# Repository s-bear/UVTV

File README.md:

# UVTV
RGB-V-UV LED display, as published in "A five-channel LED display to investigate UV perception" in Methods in Ecology and Evolution, 2021.

## TO DO
- Display: Compactness and seamless edge-to-edge display panelling is *not* a priority any more. There are a few places where these design goals made things quite difficult and any new production should have these changes made:
  - [ ] Point-of-Load power supply on display board for LEDs.
  - [ ] Separate LED power from TLC5955 power.
  - [ ] Increase margins and put mounting holes in sane places.
  - [ ] Use larger connectors for the flat-flex cables. Assess signal integrity and see if more conductors would be useful for shielding.
  - [ ] Another layer of PCB might be in order to ease routing of control signals, especially if there are signal integrity issues at higher speeds.
- Controller: A higher-speed controller is necessary to use the full potential of the display panel. There are several viable alternatives:
  1. A high-speed microcontroller module, such as the Teensy 4.1 (600 MHz), using built-in SPI or bit-banging to communicate with TLC5955 chips.
  2. A microcontroller + FPGA combo -- using the microcontroller to handle USB and FPGA to handle the TLC5955 communication.
  3. An FPGA to handle both USB and TLC5955.
- 3D Models
  - [ ] Redraw in an open source CAD tool, e.g. FreeCAD.

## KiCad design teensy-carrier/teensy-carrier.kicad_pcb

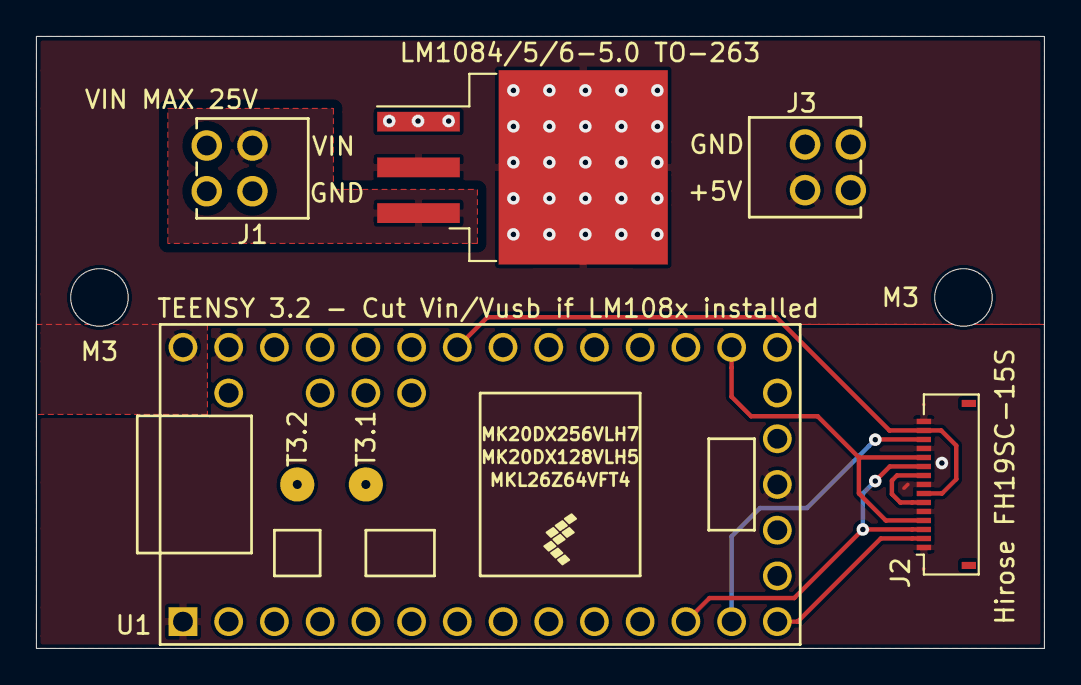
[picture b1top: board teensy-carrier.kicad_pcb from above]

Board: 2 copper layers, 56.0 x 34.0 mm, 5 parts (0 on the bottom side), 9 nets.

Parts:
J1: Conn_01x02_Male; TerminalBlock_DECA-MB312-254-2
J2: Conn_01x15_Female; Hirose_FH19SC-15S-0.5SH_1x15-1MP_P0.50mm_Horizontal
J3: Conn_01x02_Female; TerminalBlock_DECA-MB312-254-2
U1: Teensy3.2; Teensy30_31_32_LC
U2: LM1084-5.0; TO-263-3_TabPin2

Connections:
+5V: J3.2, U1.33, U2.2
/GCLK: J2.7, J2.14, U1.27
/LAT: J2.3, J2.10, U1.12
/SCLK: J2.4, J2.11, U1.21
/SIN1: J2.13, U1.13
/SOUT1_SIN2: J2.6, J2.9
/SOUT2: J2.2, U1.14
GND: J1.1, J2.1, J2.5, J2.8, J2.12, J2.15, J3.1, U1.1, U1.17, U1.32, U2.1
unnamed: J1.2, U2.3

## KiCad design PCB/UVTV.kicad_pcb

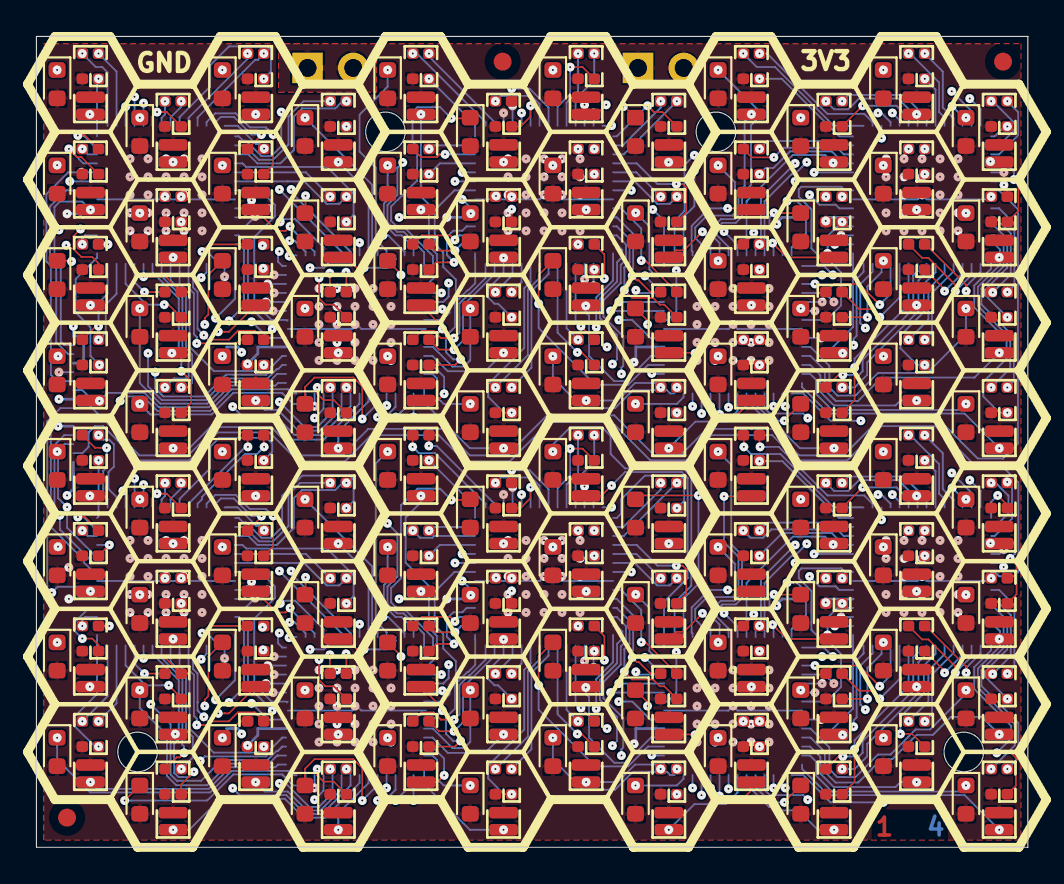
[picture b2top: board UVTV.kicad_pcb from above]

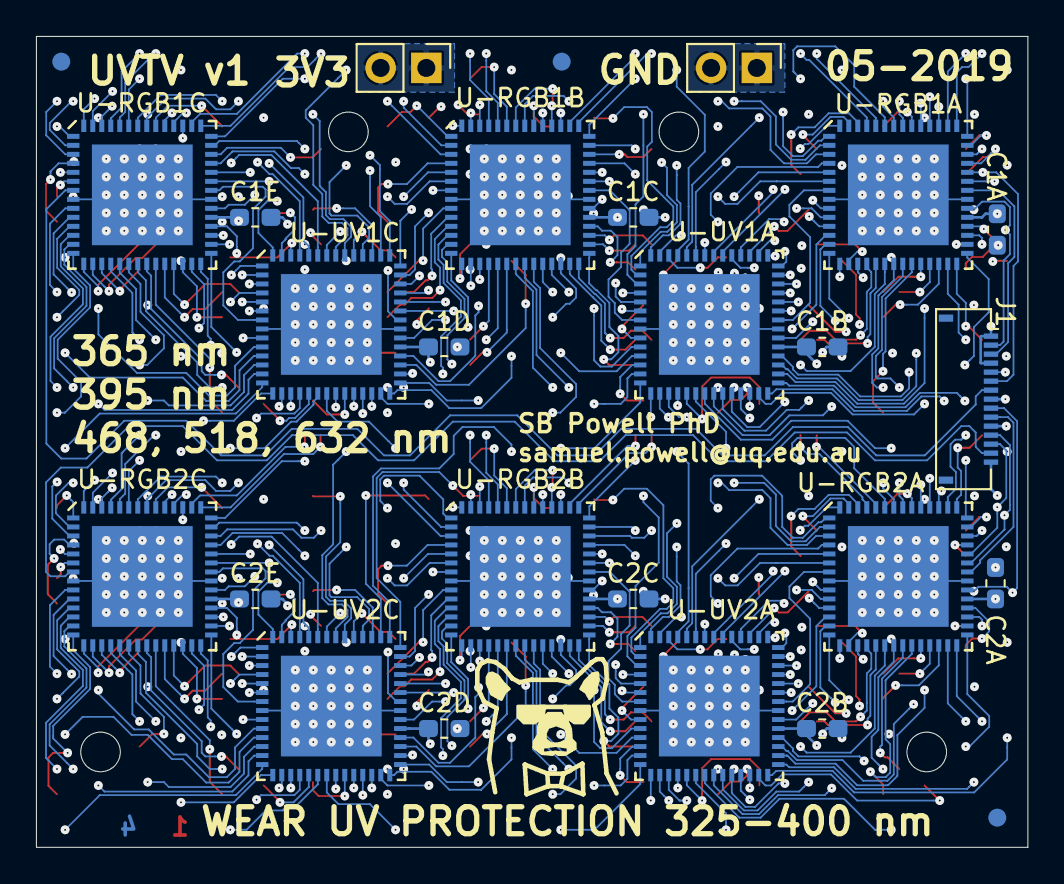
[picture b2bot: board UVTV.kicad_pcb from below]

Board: 4 copper layers, 55.1 x 45.0 mm, 321 parts (26 on the bottom side), 500 nets.

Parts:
C1A, C1B, C1C, C1D, C1E, C2A, C2B, C2C, C2D, C2E: 0.1u; C_0603_1608Metric_Pad1.05x0.95mm_HandSolder
FID1, FID2, FID3, FID4, FID5, FID6: Fiducial_1mm_Dia_2mm_Outer
J1: Conn_01x15; Hirose_FH19SC-15S-0.5SH_1x15-1MP_P0.50mm_Horizontal
J2: Conn_01x02; PinHeader_1x02_P2.54mm_Vertical
J3: Conn_01x03; PinHeader_1x02_P2.54mm_Vertical
MH1A, MH1B, MH2A, MH2B: MountingHole; MountingHole_2.2mm_M2
RGB1A0, RGB1A1, RGB1A2, RGB1A3, RGB1A4, RGB1A5, RGB1A6, RGB1A7, RGB1A8, RGB1A9, RGB1A10, RGB1A11, RGB1A12, RGB1A13, RGB1A14, RGB1A15, RGB1B0, RGB1B1, RGB1B2, RGB1B3, RGB1B4, RGB1B5, RGB1B6, RGB1B7, RGB1B8, RGB1B9, RGB1B10, RGB1B11, RGB1B12, RGB1B13, RGB1B14, RGB1B15, RGB1C0, RGB1C1, RGB1C2, RGB1C3, RGB1C4, RGB1C5, RGB1C6, RGB1C7, RGB1C8, RGB1C9, RGB1C10, RGB1C11, RGB1C12, RGB1C13, RGB1C14, RGB1C15, RGB2A0, RGB2A1, RGB2A2, RGB2A3, RGB2A4, RGB2A5, RGB2A6, RGB2A7, RGB2A8, RGB2A9, RGB2A10, RGB2A11, RGB2A12, RGB2A13, RGB2A14, RGB2A15, RGB2B0, RGB2B1, RGB2B2, RGB2B3, RGB2B4, RGB2B5, RGB2B6, RGB2B7, RGB2B8, RGB2B9, RGB2B10, RGB2B11, RGB2B12, RGB2B13, RGB2B14, RGB2B15, RGB2C0, RGB2C1, RGB2C2, RGB2C3, RGB2C4, RGB2C5, RGB2C6, RGB2C7, RGB2C8, RGB2C9, RGB2C10, RGB2C11, RGB2C12, RGB2C13, RGB2C14, RGB2C15: EAST1616RGB; EAST1616RGBA
U-RGB1A, U-RGB1B, U-RGB1C, U-RGB2A, U-RGB2B, U-RGB2C: TLC5955-RTQ; QFN-56-1EP_8x8mm_P0.5mm_EP5.6x5.6mm
U-UV1A, U-UV1C, U-UV2A, U-UV2C: TLC5955-RTQ; QFN-56-1EP_8x8mm_P0.5mm_EP5.6x5.6mm
UV1A0, UV1A1, UV1A2, UV1A3, UV1A4, UV1A5, UV1A6, UV1A7, UV1A8, UV1A9, UV1A10, UV1A11, UV1A12, UV1A13, UV1A14, UV1A15, UV1B0, UV1B1, UV1B2, UV1B3, UV1B4, UV1B5, UV1B6, UV1B7, UV1B8, UV1B9, UV1B10, UV1B11, UV1B12, UV1B13, UV1B14, UV1B15, UV1C0, UV1C1, UV1C2, UV1C3, UV1C4, UV1C5, UV1C6, UV1C7, UV1C8, UV1C9, UV1C10, UV1C11, UV1C12, UV1C13, UV1C14, UV1C15, UV2A0, UV2A1, UV2A2, UV2A3, UV2A4, UV2A5, UV2A6, UV2A7, UV2A8, UV2A9, UV2A10, UV2A11, UV2A12, UV2A13, UV2A14, UV2A15, UV2B0, UV2B1, UV2B2, UV2B3, UV2B4, UV2B5, UV2B6, UV2B7, UV2B8, UV2B9, UV2B10, UV2B11, UV2B12, UV2B13, UV2B14, UV2B15, UV2C0, UV2C1, UV2C2, UV2C3, UV2C4, UV2C5, UV2C6, UV2C7, UV2C8, UV2C9, UV2C10, UV2C11, UV2C12, UV2C13, UV2C14, UV2C15: VLMU1610-365; D_0606_1616Metric
V1A0, V1A1, V1A2, V1A3, V1A4, V1A5, V1A6, V1A7, V1A8, V1A9, V1A10, V1A11, V1A12, V1A13, V1A14, V1A15, V1B0, V1B1, V1B2, V1B3, V1B4, V1B5, V1B6, V1B7, V1B8, V1B9, V1B10, V1B11, V1B12, V1B13, V1B14, V1B15, V1C0, V1C1, V1C2, V1C3, V1C4, V1C5, V1C6, V1C7, V1C8, V1C9, V1C10, V1C11, V1C12, V1C13, V1C14, V1C15, V2A0, V2A1, V2A2, V2A3, V2A4, V2A5, V2A6, V2A7, V2A8, V2A9, V2A10, V2A11, V2A12, V2A13, V2A14, V2A15, V2B0, V2B1, V2B2, V2B3, V2B4, V2B5, V2B6, V2B7, V2B8, V2B9, V2B10, V2B11, V2B12, V2B13, V2B14, V2B15, V2C0, V2C1, V2C2, V2C3, V2C4, V2C5, V2C6, V2C7, V2C8, V2C9, V2C10, V2C11, V2C12, V2C13, V2C14, V2C15: SM0603UV-395; LED_0603_1608Metric

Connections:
+3V3: C1A.1, C1B.1, C1C.1, C1D.1, C1E.1, C2A.1, C2B.1, C2C.1, C2D.1, C2E.1, J3.1, J3.2, RGB1A0.3, RGB1A1.3, RGB1A2.3, RGB1A3.3, RGB1A4.3, RGB1A5.3, RGB1A6.3, RGB1A7.3, RGB1A8.3, RGB1A9.3, RGB1A10.3, RGB1A11.3, RGB1A12.3, RGB1A13.3, RGB1A14.3, RGB1A15.3, RGB1B0.3, RGB1B1.3, RGB1B2.3, RGB1B3.3, RGB1B4.3, RGB1B5.3, RGB1B6.3, RGB1B7.3, RGB1B8.3, RGB1B9.3, RGB1B10.3, RGB1B11.3, RGB1B12.3, RGB1B13.3, RGB1B14.3, RGB1B15.3, RGB1C0.3, RGB1C1.3, RGB1C2.3, RGB1C3.3, RGB1C4.3, RGB1C5.3, RGB1C6.3, RGB1C7.3, RGB1C8.3, RGB1C9.3, RGB1C10.3, RGB1C11.3, RGB1C12.3, RGB1C13.3, RGB1C14.3, RGB1C15.3, RGB2A0.3, RGB2A1.3, RGB2A2.3, RGB2A3.3, RGB2A4.3, RGB2A5.3, RGB2A6.3, RGB2A7.3, RGB2A8.3, RGB2A9.3, RGB2A10.3, RGB2A11.3, RGB2A12.3, RGB2A13.3, RGB2A14.3, RGB2A15.3, RGB2B0.3, RGB2B1.3, RGB2B2.3, RGB2B3.3, RGB2B4.3, RGB2B5.3, RGB2B6.3, RGB2B7.3, RGB2B8.3, RGB2B9.3, RGB2B10.3, RGB2B11.3, RGB2B12.3, RGB2B13.3, RGB2B14.3, RGB2B15.3, RGB2C0.3, RGB2C1.3, RGB2C2.3, RGB2C3.3, RGB2C4.3, RGB2C5.3, RGB2C6.3, RGB2C7.3, RGB2C8.3, RGB2C9.3, RGB2C10.3, RGB2C11.3, RGB2C12.3, RGB2C13.3, RGB2C14.3, RGB2C15.3, U-RGB1A.33, U-RGB1B.33, U-RGB1C.33, U-RGB2A.33, U-RGB2B.33, U-RGB2C.33, U-UV1A.33, U-UV1C.33, U-UV2A.33, U-UV2C.33, UV1A0.2, UV1A1.2, UV1A2.2, UV1A3.2, UV1A4.2, UV1A5.2, UV1A6.2, UV1A7.2, UV1A8.2, UV1A9.2, UV1A10.2, UV1A11.2, UV1A12.2, UV1A13.2, UV1A14.2, UV1A15.2, UV1B0.2, UV1B1.2, UV1B2.2, UV1B3.2, UV1B4.2, UV1B5.2, UV1B6.2, UV1B7.2, UV1B8.2, UV1B9.2, UV1B10.2, UV1B11.2, UV1B12.2, UV1B13.2, UV1B14.2, UV1B15.2, UV1C0.2, UV1C1.2, UV1C2.2, UV1C3.2, UV1C4.2, UV1C5.2, UV1C6.2, UV1C7.2, UV1C8.2, UV1C9.2, UV1C10.2, UV1C11.2, UV1C12.2, UV1C13.2, UV1C14.2, UV1C15.2, UV2A0.2, UV2A1.2, UV2A2.2, UV2A3.2, UV2A4.2, UV2A5.2, UV2A6.2, UV2A7.2, UV2A8.2, UV2A9.2, UV2A10.2, UV2A11.2, UV2A12.2, UV2A13.2, UV2A14.2, UV2A15.2, UV2B0.2, UV2B1.2, UV2B2.2, UV2B3.2, UV2B4.2, UV2B5.2, UV2B6.2, UV2B7.2, UV2B8.2, UV2B9.2, UV2B10.2, UV2B11.2, UV2B12.2, UV2B13.2, UV2B14.2, UV2B15.2, UV2C0.2, UV2C1.2, UV2C2.2, UV2C3.2, UV2C4.2, UV2C5.2, UV2C6.2, UV2C7.2, UV2C8.2, UV2C9.2, UV2C10.2, UV2C11.2, UV2C12.2, UV2C13.2, UV2C14.2, UV2C15.2, V1A0.2, V1A1.2, V1A2.2, V1A3.2, V1A4.2, V1A5.2, V1A6.2, V1A7.2, V1A8.2, V1A9.2, V1A10.2, V1A11.2, V1A12.2, V1A13.2, V1A14.2, V1A15.2, V1B0.2, V1B1.2, V1B2.2, V1B3.2, V1B4.2, V1B5.2, V1B6.2, V1B7.2, V1B8.2, V1B9.2, V1B10.2, V1B11.2, V1B12.2, V1B13.2, V1B14.2, V1B15.2, V1C0.2, V1C1.2, V1C2.2, V1C3.2, V1C4.2, V1C5.2, V1C6.2, V1C7.2, V1C8.2, V1C9.2, V1C10.2, V1C11.2, V1C12.2, V1C13.2, V1C14.2, V1C15.2, V2A0.2, V2A1.2, V2A2.2, V2A3.2, V2A4.2, V2A5.2, V2A6.2, V2A7.2, V2A8.2, V2A9.2, V2A10.2, V2A11.2, V2A12.2, V2A13.2, V2A14.2, V2A15.2, V2B0.2, V2B1.2, V2B2.2, V2B3.2, V2B4.2, V2B5.2, V2B6.2, V2B7.2, V2B8.2, V2B9.2, V2B10.2, V2B11.2, V2B12.2, V2B13.2, V2B14.2, V2B15.2, V2C0.2, V2C1.2, V2C2.2, V2C3.2, V2C4.2, V2C5.2, V2C6.2, V2C7.2, V2C8.2, V2C9.2, V2C10.2, V2C11.2, V2C12.2, V2C13.2, V2C14.2, V2C15.2
/B1A0: RGB1A0.1, U-RGB1A.42
/B1A1: RGB1A1.1, U-RGB1A.48
/B1A2: RGB1A2.1, U-RGB1A.51
/B1A3: RGB1A3.1, U-RGB1A.1
/B1A4: RGB1A4.1, U-RGB1A.39
/B1A5: RGB1A5.1, U-RGB1A.45
/B1A6: RGB1A6.1, U-RGB1A.54
/B1A7: RGB1A7.1, U-RGB1A.4
/B1A8: RGB1A8.1, U-RGB1A.32
/B1A9: RGB1A9.1, U-RGB1A.26
/B1A10: RGB1A10.1, U-RGB1A.17
/B1A11: RGB1A11.1, U-RGB1A.11
/B1A12: RGB1A12.1, U-RGB1A.29
/B1A13: RGB1A13.1, U-RGB1A.23
/B1A14: RGB1A14.1, U-RGB1A.20
/B1A15: RGB1A15.1, U-RGB1A.14
/B1B0: RGB1B0.1, U-RGB1B.42
/B1B1: RGB1B1.1, U-RGB1B.48
/B1B2: RGB1B2.1, U-RGB1B.51
/B1B3: RGB1B3.1, U-RGB1B.1
/B1B4: RGB1B4.1, U-RGB1B.39
/B1B5: RGB1B5.1, U-RGB1B.45
/B1B6: RGB1B6.1, U-RGB1B.54
/B1B7: RGB1B7.1, U-RGB1B.4
/B1B8: RGB1B8.1, U-RGB1B.32
/B1B9: RGB1B9.1, U-RGB1B.26
/B1B10: RGB1B10.1, U-RGB1B.17
/B1B11: RGB1B11.1, U-RGB1B.11
/B1B12: RGB1B12.1, U-RGB1B.29
/B1B13: RGB1B13.1, U-RGB1B.23
/B1B14: RGB1B14.1, U-RGB1B.20
/B1B15: RGB1B15.1, U-RGB1B.14
/B1C0: RGB1C0.1, U-RGB1C.42
/B1C1: RGB1C1.1, U-RGB1C.48
/B1C2: RGB1C2.1, U-RGB1C.51
/B1C3: RGB1C3.1, U-RGB1C.1
/B1C4: RGB1C4.1, U-RGB1C.39
/B1C5: RGB1C5.1, U-RGB1C.45
/B1C6: RGB1C6.1, U-RGB1C.54
/B1C7: RGB1C7.1, U-RGB1C.4
/B1C8: RGB1C8.1, U-RGB1C.32
/B1C9: RGB1C9.1, U-RGB1C.26
/B1C10: RGB1C10.1, U-RGB1C.17
/B1C11: RGB1C11.1, U-RGB1C.11
/B1C12: RGB1C12.1, U-RGB1C.29
/B1C13: RGB1C13.1, U-RGB1C.23
/B1C14: RGB1C14.1, U-RGB1C.20
/B1C15: RGB1C15.1, U-RGB1C.14
/B2A0: RGB2A0.1, U-RGB2A.42
/B2A1: RGB2A1.1, U-RGB2A.48
/B2A2: RGB2A2.1, U-RGB2A.51
/B2A3: RGB2A3.1, U-RGB2A.1
/B2A4: RGB2A4.1, U-RGB2A.39
/B2A5: RGB2A5.1, U-RGB2A.45
/B2A6: RGB2A6.1, U-RGB2A.54
/B2A7: RGB2A7.1, U-RGB2A.4
/B2A8: RGB2A8.1, U-RGB2A.32
/B2A9: RGB2A9.1, U-RGB2A.26
/B2A10: RGB2A10.1, U-RGB2A.17
/B2A11: RGB2A11.1, U-RGB2A.11
/B2A12: RGB2A12.1, U-RGB2A.29
/B2A13: RGB2A13.1, U-RGB2A.23
/B2A14: RGB2A14.1, U-RGB2A.20
/B2A15: RGB2A15.1, U-RGB2A.14
/B2B0: RGB2B0.1, U-RGB2B.42
/B2B1: RGB2B1.1, U-RGB2B.48
/B2B2: RGB2B2.1, U-RGB2B.51
/B2B3: RGB2B3.1, U-RGB2B.1
/B2B4: RGB2B4.1, U-RGB2B.39
/B2B5: RGB2B5.1, U-RGB2B.45
/B2B6: RGB2B6.1, U-RGB2B.54
/B2B7: RGB2B7.1, U-RGB2B.4
/B2B8: RGB2B8.1, U-RGB2B.32
/B2B9: RGB2B9.1, U-RGB2B.26
/B2B10: RGB2B10.1, U-RGB2B.17
/B2B11: RGB2B11.1, U-RGB2B.11
/B2B12: RGB2B12.1, U-RGB2B.29
/B2B13: RGB2B13.1, U-RGB2B.23
/B2B14: RGB2B14.1, U-RGB2B.20
/B2B15: RGB2B15.1, U-RGB2B.14
/B2C0: RGB2C0.1, U-RGB2C.42
/B2C1: RGB2C1.1, U-RGB2C.48
/B2C2: RGB2C2.1, U-RGB2C.51
/B2C3: RGB2C3.1, U-RGB2C.1
/B2C4: RGB2C4.1, U-RGB2C.39
/B2C5: RGB2C5.1, U-RGB2C.45
/B2C6: RGB2C6.1, U-RGB2C.54
/B2C7: RGB2C7.1, U-RGB2C.4
/B2C8: RGB2C8.1, U-RGB2C.32
/B2C9: RGB2C9.1, U-RGB2C.26
/B2C10: RGB2C10.1, U-RGB2C.17
/B2C11: RGB2C11.1, U-RGB2C.11
/B2C12: RGB2C12.1, U-RGB2C.29
/B2C13: RGB2C13.1, U-RGB2C.23
/B2C14: RGB2C14.1, U-RGB2C.20
/B2C15: RGB2C15.1, U-RGB2C.14
/G1A0: RGB1A0.2, U-RGB1A.44
/G1A1: RGB1A1.2, U-RGB1A.50
/G1A2: RGB1A2.2, U-RGB1A.53
/G1A3: RGB1A3.2, U-RGB1A.3
/G1A4: RGB1A4.2, U-RGB1A.41
/G1A5: RGB1A5.2, U-RGB1A.47
/G1A6: RGB1A6.2, U-RGB1A.56
/G1A7: RGB1A7.2, U-RGB1A.6
/G1A8: RGB1A8.2, U-RGB1A.30
/G1A9: RGB1A9.2, U-RGB1A.24
/G1A10: RGB1A10.2, U-RGB1A.15
/G1A11: RGB1A11.2, U-RGB1A.9
/G1A12: RGB1A12.2, U-RGB1A.27
/G1A13: RGB1A13.2, U-RGB1A.21
/G1A14: RGB1A14.2, U-RGB1A.18
/G1A15: RGB1A15.2, U-RGB1A.12
/G1B0: RGB1B0.2, U-RGB1B.44
/G1B1: RGB1B1.2, U-RGB1B.50
/G1B2: RGB1B2.2, U-RGB1B.53
/G1B3: RGB1B3.2, U-RGB1B.3
/G1B4: RGB1B4.2, U-RGB1B.41
/G1B5: RGB1B5.2, U-RGB1B.47
/G1B6: RGB1B6.2, U-RGB1B.56
/G1B7: RGB1B7.2, U-RGB1B.6
/G1B8: RGB1B8.2, U-RGB1B.30
/G1B9: RGB1B9.2, U-RGB1B.24
/G1B10: RGB1B10.2, U-RGB1B.15
/G1B11: RGB1B11.2, U-RGB1B.9
/G1B12: RGB1B12.2, U-RGB1B.27
/G1B13: RGB1B13.2, U-RGB1B.21
/G1B14: RGB1B14.2, U-RGB1B.18
/G1B15: RGB1B15.2, U-RGB1B.12
/G1C0: RGB1C0.2, U-RGB1C.44
/G1C1: RGB1C1.2, U-RGB1C.50
/G1C2: RGB1C2.2, U-RGB1C.53
/G1C3: RGB1C3.2, U-RGB1C.3
/G1C4: RGB1C4.2, U-RGB1C.41
/G1C5: RGB1C5.2, U-RGB1C.47
/G1C6: RGB1C6.2, U-RGB1C.56
/G1C7: RGB1C7.2, U-RGB1C.6
/G1C8: RGB1C8.2, U-RGB1C.30
/G1C9: RGB1C9.2, U-RGB1C.24
/G1C10: RGB1C10.2, U-RGB1C.15
/G1C11: RGB1C11.2, U-RGB1C.9
/G1C12: RGB1C12.2, U-RGB1C.27
/G1C13: RGB1C13.2, U-RGB1C.21
/G1C14: RGB1C14.2, U-RGB1C.18
/G1C15: RGB1C15.2, U-RGB1C.12
/G2A0: RGB2A0.2, U-RGB2A.44
/G2A1: RGB2A1.2, U-RGB2A.50
/G2A2: RGB2A2.2, U-RGB2A.53
/G2A3: RGB2A3.2, U-RGB2A.3
/G2A4: RGB2A4.2, U-RGB2A.41
/G2A5: RGB2A5.2, U-RGB2A.47
/G2A6: RGB2A6.2, U-RGB2A.56
/G2A7: RGB2A7.2, U-RGB2A.6
/G2A8: RGB2A8.2, U-RGB2A.30
/G2A9: RGB2A9.2, U-RGB2A.24
/G2A10: RGB2A10.2, U-RGB2A.15
/G2A11: RGB2A11.2, U-RGB2A.9
/G2A12: RGB2A12.2, U-RGB2A.27
/G2A13: RGB2A13.2, U-RGB2A.21
/G2A14: RGB2A14.2, U-RGB2A.18
/G2A15: RGB2A15.2, U-RGB2A.12
/G2B0: RGB2B0.2, U-RGB2B.44
/G2B1: RGB2B1.2, U-RGB2B.50
/G2B2: RGB2B2.2, U-RGB2B.53
/G2B3: RGB2B3.2, U-RGB2B.3
/G2B4: RGB2B4.2, U-RGB2B.41
/G2B5: RGB2B5.2, U-RGB2B.47
/G2B6: RGB2B6.2, U-RGB2B.56
/G2B7: RGB2B7.2, U-RGB2B.6
/G2B8: RGB2B8.2, U-RGB2B.30
/G2B9: RGB2B9.2, U-RGB2B.24
/G2B10: RGB2B10.2, U-RGB2B.15
/G2B11: RGB2B11.2, U-RGB2B.9
/G2B12: RGB2B12.2, U-RGB2B.27
/G2B13: RGB2B13.2, U-RGB2B.21
/G2B14: RGB2B14.2, U-RGB2B.18
/G2B15: RGB2B15.2, U-RGB2B.12
/G2C0: RGB2C0.2, U-RGB2C.44
/G2C1: RGB2C1.2, U-RGB2C.50
/G2C2: RGB2C2.2, U-RGB2C.53
/G2C3: RGB2C3.2, U-RGB2C.3
/G2C4: RGB2C4.2, U-RGB2C.41
/G2C5: RGB2C5.2, U-RGB2C.47
/G2C6: RGB2C6.2, U-RGB2C.56
/G2C7: RGB2C7.2, U-RGB2C.6
/G2C8: RGB2C8.2, U-RGB2C.30
/G2C9: RGB2C9.2, U-RGB2C.24
/G2C10: RGB2C10.2, U-RGB2C.15
/G2C11: RGB2C11.2, U-RGB2C.9
/G2C12: RGB2C12.2, U-RGB2C.27
/G2C13: RGB2C13.2, U-RGB2C.21
/G2C14: RGB2C14.2, U-RGB2C.18
/G2C15: RGB2C15.2, U-RGB2C.12
/GSCLK1: J1.2, U-RGB1A.34, U-RGB1B.34, U-RGB1C.34, U-UV1A.34, U-UV1C.34
/GSCLK2: J1.9, U-RGB2A.34, U-RGB2B.34, U-RGB2C.34, U-UV2A.34, U-UV2C.34
/LAT1: J1.6, U-RGB1A.38, U-RGB1B.38, U-RGB1C.38, U-UV1A.38, U-UV1C.38
/LAT2: J1.13, U-RGB2A.38, U-RGB2B.38, U-RGB2C.38, U-UV2A.38, U-UV2C.38
/R1A0: RGB1A0.4, U-RGB1A.43
/R1A1: RGB1A1.4, U-RGB1A.49
/R1A2: RGB1A2.4, U-RGB1A.52
/R1A3: RGB1A3.4, U-RGB1A.2
/R1A4: RGB1A4.4, U-RGB1A.40
/R1A5: RGB1A5.4, U-RGB1A.46
/R1A6: RGB1A6.4, U-RGB1A.55
/R1A7: RGB1A7.4, U-RGB1A.5
/R1A8: RGB1A8.4, U-RGB1A.31
/R1A9: RGB1A9.4, U-RGB1A.25
/R1A10: RGB1A10.4, U-RGB1A.16
/R1A11: RGB1A11.4, U-RGB1A.10
/R1A12: RGB1A12.4, U-RGB1A.28
/R1A13: RGB1A13.4, U-RGB1A.22
/R1A14: RGB1A14.4, U-RGB1A.19
/R1A15: RGB1A15.4, U-RGB1A.13
/R1B0: RGB1B0.4, U-RGB1B.43
/R1B1: RGB1B1.4, U-RGB1B.49
/R1B2: RGB1B2.4, U-RGB1B.52
/R1B3: RGB1B3.4, U-RGB1B.2
/R1B4: RGB1B4.4, U-RGB1B.40
/R1B5: RGB1B5.4, U-RGB1B.46
/R1B6: RGB1B6.4, U-RGB1B.55
/R1B7: RGB1B7.4, U-RGB1B.5
/R1B8: RGB1B8.4, U-RGB1B.31
/R1B9: RGB1B9.4, U-RGB1B.25
/R1B10: RGB1B10.4, U-RGB1B.16
/R1B11: RGB1B11.4, U-RGB1B.10
/R1B12: RGB1B12.4, U-RGB1B.28
/R1B13: RGB1B13.4, U-RGB1B.22
/R1B14: RGB1B14.4, U-RGB1B.19
/R1B15: RGB1B15.4, U-RGB1B.13
/R1C0: RGB1C0.4, U-RGB1C.43
/R1C1: RGB1C1.4, U-RGB1C.49
/R1C2: RGB1C2.4, U-RGB1C.52
/R1C3: RGB1C3.4, U-RGB1C.2
/R1C4: RGB1C4.4, U-RGB1C.40
/R1C5: RGB1C5.4, U-RGB1C.46
/R1C6: RGB1C6.4, U-RGB1C.55
/R1C7: RGB1C7.4, U-RGB1C.5
/R1C8: RGB1C8.4, U-RGB1C.31
/R1C9: RGB1C9.4, U-RGB1C.25
/R1C10: RGB1C10.4, U-RGB1C.16
/R1C11: RGB1C11.4, U-RGB1C.10
/R1C12: RGB1C12.4, U-RGB1C.28
/R1C13: RGB1C13.4, U-RGB1C.22
/R1C14: RGB1C14.4, U-RGB1C.19
/R1C15: RGB1C15.4, U-RGB1C.13
/R2A0: RGB2A0.4, U-RGB2A.43
/R2A1: RGB2A1.4, U-RGB2A.49
/R2A2: RGB2A2.4, U-RGB2A.52
/R2A3: RGB2A3.4, U-RGB2A.2
/R2A4: RGB2A4.4, U-RGB2A.40
/R2A5: RGB2A5.4, U-RGB2A.46
/R2A6: RGB2A6.4, U-RGB2A.55
/R2A7: RGB2A7.4, U-RGB2A.5
/R2A8: RGB2A8.4, U-RGB2A.31
/R2A9: RGB2A9.4, U-RGB2A.25
/R2A10: RGB2A10.4, U-RGB2A.16
/R2A11: RGB2A11.4, U-RGB2A.10
/R2A12: RGB2A12.4, U-RGB2A.28
/R2A13: RGB2A13.4, U-RGB2A.22
/R2A14: RGB2A14.4, U-RGB2A.19
/R2A15: RGB2A15.4, U-RGB2A.13
/R2B0: RGB2B0.4, U-RGB2B.43
/R2B1: RGB2B1.4, U-RGB2B.49
/R2B2: RGB2B2.4, U-RGB2B.52
/R2B3: RGB2B3.4, U-RGB2B.2
/R2B4: RGB2B4.4, U-RGB2B.40
/R2B5: RGB2B5.4, U-RGB2B.46
/R2B6: RGB2B6.4, U-RGB2B.55
/R2B7: RGB2B7.4, U-RGB2B.5
/R2B8: RGB2B8.4, U-RGB2B.31
/R2B9: RGB2B9.4, U-RGB2B.25
/R2B10: RGB2B10.4, U-RGB2B.16
/R2B11: RGB2B11.4, U-RGB2B.10
/R2B12: RGB2B12.4, U-RGB2B.28
/R2B13: RGB2B13.4, U-RGB2B.22
/R2B14: RGB2B14.4, U-RGB2B.19
/R2B15: RGB2B15.4, U-RGB2B.13
/R2C0: RGB2C0.4, U-RGB2C.43
/R2C1: RGB2C1.4, U-RGB2C.49
/R2C2: RGB2C2.4, U-RGB2C.52
/R2C3: RGB2C3.4, U-RGB2C.2
/R2C4: RGB2C4.4, U-RGB2C.40
/R2C5: RGB2C5.4, U-RGB2C.46
/R2C6: RGB2C6.4, U-RGB2C.55
/R2C7: RGB2C7.4, U-RGB2C.5
/R2C8: RGB2C8.4, U-RGB2C.31
/R2C9: RGB2C9.4, U-RGB2C.25
/R2C10: RGB2C10.4, U-RGB2C.16
/R2C11: RGB2C11.4, U-RGB2C.10
/R2C12: RGB2C12.4, U-RGB2C.28
/R2C13: RGB2C13.4, U-RGB2C.22
/R2C14: RGB2C14.4, U-RGB2C.19
/R2C15: RGB2C15.4, U-RGB2C.13
/SCLK1: J1.5, U-RGB1A.37, U-RGB1B.37, U-RGB1C.37, U-UV1A.37, U-UV1C.37
/SCLK2: J1.12, U-RGB2A.37, U-RGB2B.37, U-RGB2C.37, U-UV2A.37, U-UV2C.37
/SIN1: J1.3, U-RGB1A.36
/SIN2: J1.10, U-RGB2A.36
/SOUT1: J1.7, U-RGB1C.7
/SOUT2: J1.14, U-RGB2C.7
/UV1A0: U-UV1A.42, UV1A0.1
/UV1A1: U-UV1A.48, UV1A1.1
/UV1A2: U-UV1A.51, UV1A2.1
/UV1A3: U-UV1A.1, UV1A3.1
/UV1A4: U-UV1A.39, UV1A4.1
/UV1A5: U-UV1A.45, UV1A5.1
/UV1A6: U-UV1A.54, UV1A6.1
/UV1A7: U-UV1A.4, UV1A7.1
/UV1A8: U-UV1A.32, UV1A8.1
/UV1A9: U-UV1A.26, UV1A9.1
/UV1A10: U-UV1A.17, UV1A10.1
/UV1A11: U-UV1A.11, UV1A11.1
/UV1A12: U-UV1A.29, UV1A12.1
/UV1A13: U-UV1A.23, UV1A13.1
/UV1A14: U-UV1A.20, UV1A14.1
/UV1A15: U-UV1A.14, UV1A15.1
/UV1B0: U-UV1A.50, UV1B0.1
/UV1B1: U-UV1A.3, UV1B1.1
/UV1B2: U-UV1A.47, UV1B2.1
/UV1B3: U-UV1A.6, UV1B3.1
/UV1B4: U-UV1A.24, UV1B4.1
/UV1B5: U-UV1A.9, UV1B5.1
/UV1B6: U-UV1A.21, UV1B6.1
/UV1B7: U-UV1A.12, UV1B7.1
/UV1B8: U-UV1C.50, UV1B8.1
/UV1B9: U-UV1C.3, UV1B9.1
/UV1B10: U-UV1C.47, UV1B10.1
/UV1B11: U-UV1C.6, UV1B11.1
/UV1B12: U-UV1C.24, UV1B12.1
/UV1B13: U-UV1C.9, UV1B13.1
/UV1B14: U-UV1C.21, UV1B14.1
/UV1B15: U-UV1C.12, UV1B15.1
/UV1C0: U-UV1C.42, UV1C0.1
/UV1C1: U-UV1C.48, UV1C1.1
/UV1C2: U-UV1C.51, UV1C2.1
/UV1C3: U-UV1C.1, UV1C3.1
/UV1C4: U-UV1C.39, UV1C4.1
/UV1C5: U-UV1C.45, UV1C5.1
/UV1C6: U-UV1C.54, UV1C6.1
/UV1C7: U-UV1C.4, UV1C7.1
/UV1C8: U-UV1C.32, UV1C8.1
/UV1C9: U-UV1C.26, UV1C9.1
/UV1C10: U-UV1C.17, UV1C10.1
/UV1C11: U-UV1C.11, UV1C11.1
/UV1C12: U-UV1C.29, UV1C12.1
/UV1C13: U-UV1C.23, UV1C13.1
/UV1C14: U-UV1C.20, UV1C14.1
/UV1C15: U-UV1C.14, UV1C15.1
/UV2A0: U-UV2A.42, UV2A0.1
/UV2A1: U-UV2A.48, UV2A1.1
/UV2A2: U-UV2A.51, UV2A2.1
/UV2A3: U-UV2A.1, UV2A3.1
/UV2A4: U-UV2A.39, UV2A4.1
/UV2A5: U-UV2A.45, UV2A5.1
/UV2A6: U-UV2A.54, UV2A6.1
/UV2A7: U-UV2A.4, UV2A7.1
/UV2A8: U-UV2A.32, UV2A8.1
/UV2A9: U-UV2A.26, UV2A9.1
/UV2A10: U-UV2A.17, UV2A10.1
/UV2A11: U-UV2A.11, UV2A11.1
/UV2A12: U-UV2A.29, UV2A12.1
/UV2A13: U-UV2A.23, UV2A13.1
/UV2A14: U-UV2A.20, UV2A14.1
/UV2A15: U-UV2A.14, UV2A15.1
/UV2B0: U-UV2A.50, UV2B0.1
/UV2B1: U-UV2A.3, UV2B1.1
/UV2B2: U-UV2A.47, UV2B2.1
/UV2B3: U-UV2A.6, UV2B3.1
/UV2B4: U-UV2A.24, UV2B4.1
/UV2B5: U-UV2A.9, UV2B5.1
/UV2B6: U-UV2A.21, UV2B6.1
/UV2B7: U-UV2A.12, UV2B7.1
/UV2B8: U-UV2C.50, UV2B8.1
/UV2B9: U-UV2C.3, UV2B9.1
/UV2B10: U-UV2C.47, UV2B10.1
/UV2B11: U-UV2C.6, UV2B11.1
/UV2B12: U-UV2C.24, UV2B12.1
/UV2B13: U-UV2C.9, UV2B13.1
/UV2B14: U-UV2C.21, UV2B14.1
/UV2B15: U-UV2C.12, UV2B15.1
/UV2C0: U-UV2C.42, UV2C0.1
/UV2C1: U-UV2C.48, UV2C1.1
/UV2C2: U-UV2C.51, UV2C2.1
/UV2C3: U-UV2C.1, UV2C3.1
/UV2C4: U-UV2C.39, UV2C4.1
/UV2C5: U-UV2C.45, UV2C5.1
/UV2C6: U-UV2C.54, UV2C6.1
/UV2C7: U-UV2C.4, UV2C7.1
/UV2C8: U-UV2C.32, UV2C8.1
/UV2C9: U-UV2C.26, UV2C9.1
/UV2C10: U-UV2C.17, UV2C10.1
/UV2C11: U-UV2C.11, UV2C11.1
/UV2C12: U-UV2C.29, UV2C12.1
/UV2C13: U-UV2C.23, UV2C13.1
/UV2C14: U-UV2C.20, UV2C14.1
/UV2C15: U-UV2C.14, UV2C15.1
/V1A0: U-UV1A.43, V1A0.1
/V1A1: U-UV1A.49, V1A1.1
/V1A2: U-UV1A.52, V1A2.1
/V1A3: U-UV1A.2, V1A3.1
/V1A4: U-UV1A.40, V1A4.1
/V1A5: U-UV1A.46, V1A5.1
/V1A6: U-UV1A.55, V1A6.1
/V1A7: U-UV1A.5, V1A7.1
/V1A8: U-UV1A.31, V1A8.1
/V1A9: U-UV1A.25, V1A9.1
/V1A10: U-UV1A.16, V1A10.1
/V1A11: U-UV1A.10, V1A11.1
/V1A12: U-UV1A.28, V1A12.1
/V1A13: U-UV1A.22, V1A13.1
/V1A14: U-UV1A.19, V1A14.1
/V1A15: U-UV1A.13, V1A15.1
/V1B0: U-UV1A.44, V1B0.1
/V1B1: U-UV1A.53, V1B1.1
/V1B2: U-UV1A.41, V1B2.1
/V1B3: U-UV1A.56, V1B3.1
/V1B4: U-UV1A.30, V1B4.1
/V1B5: U-UV1A.15, V1B5.1
/V1B6: U-UV1A.27, V1B6.1
/V1B7: U-UV1A.18, V1B7.1
/V1B8: U-UV1C.44, V1B8.1
/V1B9: U-UV1C.53, V1B9.1
/V1B10: U-UV1C.41, V1B10.1
/V1B11: U-UV1C.56, V1B11.1
/V1B12: U-UV1C.30, V1B12.1
/V1B13: U-UV1C.15, V1B13.1
/V1B14: U-UV1C.27, V1B14.1
/V1B15: U-UV1C.18, V1B15.1
/V1C0: U-UV1C.43, V1C0.1
/V1C1: U-UV1C.49, V1C1.1
/V1C2: U-UV1C.52, V1C2.1
/V1C3: U-UV1C.2, V1C3.1
/V1C4: U-UV1C.40, V1C4.1
/V1C5: U-UV1C.46, V1C5.1
/V1C6: U-UV1C.55, V1C6.1
/V1C7: U-UV1C.5, V1C7.1
/V1C8: U-UV1C.31, V1C8.1
/V1C9: U-UV1C.25, V1C9.1
/V1C10: U-UV1C.16, V1C10.1
/V1C11: U-UV1C.10, V1C11.1
/V1C12: U-UV1C.28, V1C12.1
/V1C13: U-UV1C.22, V1C13.1
/V1C14: U-UV1C.19, V1C14.1
/V1C15: U-UV1C.13, V1C15.1
/V2A0: U-UV2A.43, V2A0.1
/V2A1: U-UV2A.49, V2A1.1
/V2A2: U-UV2A.52, V2A2.1
/V2A3: U-UV2A.2, V2A3.1
/V2A4: U-UV2A.40, V2A4.1
/V2A5: U-UV2A.46, V2A5.1
/V2A6: U-UV2A.55, V2A6.1
/V2A7: U-UV2A.5, V2A7.1
/V2A8: U-UV2A.31, V2A8.1
/V2A9: U-UV2A.25, V2A9.1
/V2A10: U-UV2A.16, V2A10.1
/V2A11: U-UV2A.10, V2A11.1
/V2A12: U-UV2A.28, V2A12.1
/V2A13: U-UV2A.22, V2A13.1
/V2A14: U-UV2A.19, V2A14.1
/V2A15: U-UV2A.13, V2A15.1
/V2B0: U-UV2A.44, V2B0.1
/V2B1: U-UV2A.53, V2B1.1
/V2B2: U-UV2A.41, V2B2.1
/V2B3: U-UV2A.56, V2B3.1
/V2B4: U-UV2A.30, V2B4.1
/V2B5: U-UV2A.15, V2B5.1
/V2B6: U-UV2A.27, V2B6.1
/V2B7: U-UV2A.18, V2B7.1
/V2B8: U-UV2C.44, V2B8.1
/V2B9: U-UV2C.53, V2B9.1
/V2B10: U-UV2C.41, V2B10.1
/V2B11: U-UV2C.56, V2B11.1
/V2B12: U-UV2C.30, V2B12.1
/V2B13: U-UV2C.15, V2B13.1
/V2B14: U-UV2C.27, V2B14.1
/V2B15: U-UV2C.18, V2B15.1
/V2C0: U-UV2C.43, V2C0.1
/V2C1: U-UV2C.49, V2C1.1
/V2C2: U-UV2C.52, V2C2.1
/V2C3: U-UV2C.2, V2C3.1
/V2C4: U-UV2C.40, V2C4.1
/V2C5: U-UV2C.46, V2C5.1
/V2C6: U-UV2C.55, V2C6.1
/V2C7: U-UV2C.5, V2C7.1
/V2C8: U-UV2C.31, V2C8.1
/V2C9: U-UV2C.25, V2C9.1
/V2C10: U-UV2C.16, V2C10.1
/V2C11: U-UV2C.10, V2C11.1
/V2C12: U-UV2C.28, V2C12.1
/V2C13: U-UV2C.22, V2C13.1
/V2C14: U-UV2C.19, V2C14.1
/V2C15: U-UV2C.13, V2C15.1
GND: C1A.2, C1B.2, C1C.2, C1D.2, C1E.2, C2A.2, C2B.2, C2C.2, C2D.2, C2E.2, J1.1, J1.4, J1.8, J1.11, J1.15, J2.1, J2.2, U-RGB1A.8, U-RGB1A.35, U-RGB1A.57, U-RGB1B.8, U-RGB1B.35, U-RGB1B.57, U-RGB1C.8, U-RGB1C.35, U-RGB1C.57, U-RGB2A.8, U-RGB2A.35, U-RGB2A.57, U-RGB2B.8, U-RGB2B.35, U-RGB2B.57, U-RGB2C.8, U-RGB2C.35, U-RGB2C.57, U-UV1A.8, U-UV1A.35, U-UV1A.57, U-UV1C.8, U-UV1C.35, U-UV1C.57, U-UV2A.8, U-UV2A.35, U-UV2A.57, U-UV2C.8, U-UV2C.35, U-UV2C.57
unnamed: U-RGB1A.7, U-UV1A.36
unnamed: U-RGB1B.7, U-UV1C.36
unnamed: U-RGB1B.36, U-UV1A.7
unnamed: U-RGB1C.36, U-UV1C.7
unnamed: U-RGB2A.7, U-UV2A.36
unnamed: U-RGB2B.7, U-UV2C.36
unnamed: U-RGB2B.36, U-UV2A.7
unnamed: U-RGB2C.36, U-UV2C.7

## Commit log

2019-12-02 initial commit -- KiCAD files
2019-12-02 initial commit -- software
2019-12-02 add old code
2019-12-02 Work
2019-12-02 first test, sorta working
2019-12-02 ignore pycache
2019-12-02 add teensy-carrier board
2019-12-03 fix endianness issue and spi queue issue
2019-12-03 add kicad lib files
2019-12-03 add teensy.lib
2019-12-03 work on teensy-carrier
2019-12-20 update_20_12_19
2019-12-20 add save/load for dotcorrect etc
2019-12-20 add display save/load commands
2019-12-20 fix reversed wiring
2019-12-20 random pixel example
2020-01-06 random image gen
2020-01-07 pattern gen update
2020-01-07 add make_flatfield.py
2020-01-08 add nemo drawing footprint
2020-01-08 add TerminalBlock_DECA-... footprint
2020-01-08 relative reference to footprint library
2020-01-08 fix pin ordering, use terminal blocks instead of pin headers for power entry/supply
2020-01-08 archive v1 gerbers, generate v2 gerbers
2020-01-08 geometry is height, width, channels
2020-01-08 store SPI Frequency and Serial # in EEPROM
2020-01-08 change pixel addressing to y,x,c
2020-01-13 add draw_pattern()
2020-01-14 14-01-20
2020-01-20 add serial number etc in eeprom
2020-01-20 remove code unrelated to testing
2020-01-20 change files
2020-11-09 changes for 2020-11-08 submission
2020-12-21 organize before publication
2020-12-21 Add board 2 data 0
2020-12-21 add board 2 data/1
2020-12-21 Add board 2 data/2
2020-12-21 add 'board 2 data' summary info and README
2021-01-06 Update README.md
    Add Zenodo badge
2021-01-28 Add 3D models
2021-02-22 Add OpenSCAD models to replace Inventor.
2022-04-01 Add (unused) Verilog FPGA files for posterity
2022-04-01 Add missing FPGA files
2022-04-26 auto-detect serial port
2022-05-19 Use TkAgg backend instead of Qt to remove dependency
2023-01-20 fix SCPI parsing (fix error when , appears in arbitrary data block), add functions to translate codes back to real numbers
2023-01-20 refactor test_panel.py to improve safety
    - explicit operating modes rather than boolean flags (reset_config was dangerous!)
    - check for files before overwriting them (reset_config was dangerous!)
    - check for serial number mismatch between board & config file before programming
    - add 'download' mode to pull config data from the board
    - add 'test-board' mode to test config data stored on the board
